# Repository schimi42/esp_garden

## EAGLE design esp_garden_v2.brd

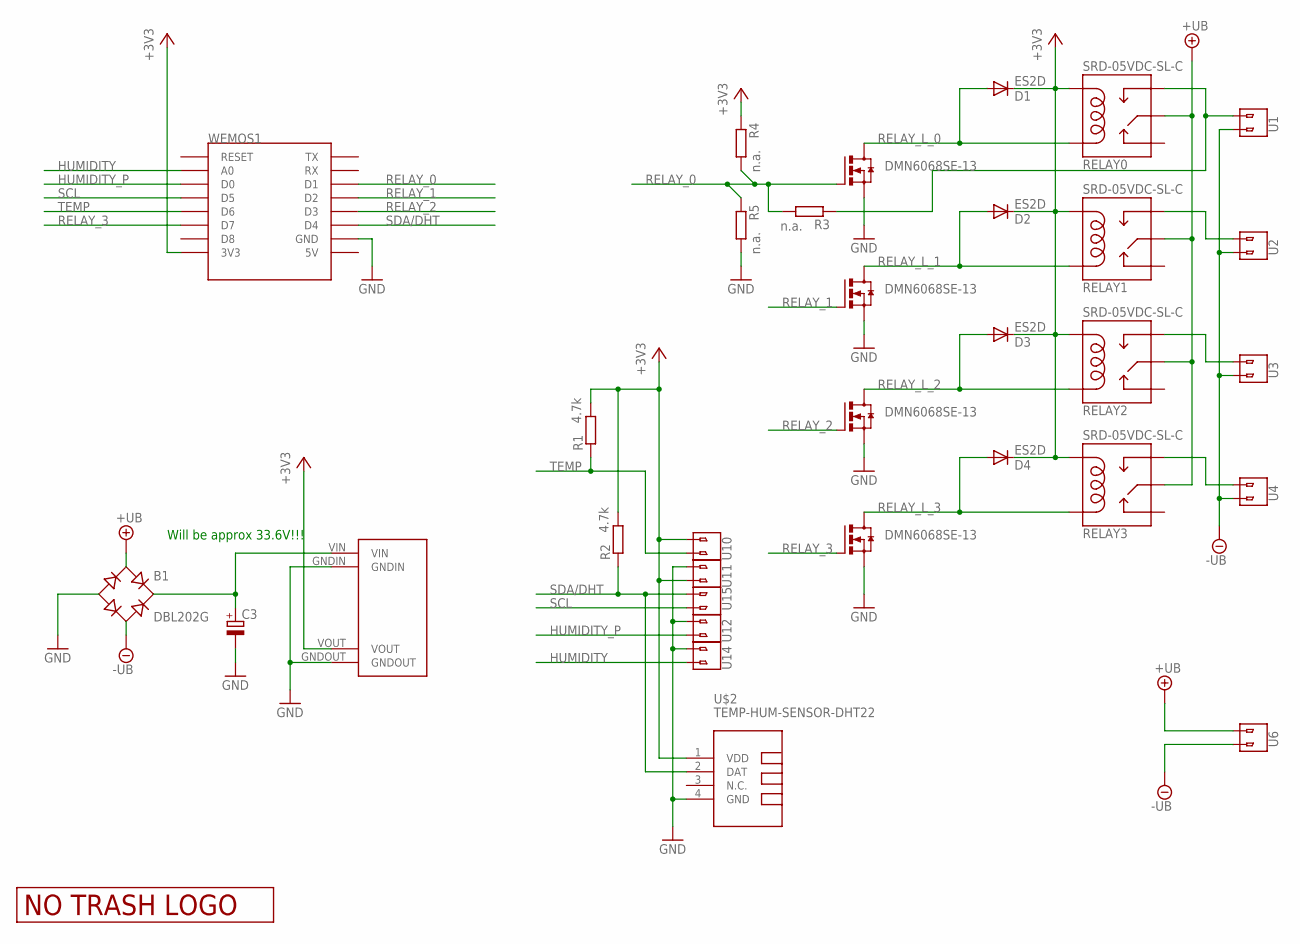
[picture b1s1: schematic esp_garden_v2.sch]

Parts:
B1: DBL202G; DB
C3: CPOL-EU150CLZ-0810; 150CLZ-0810
D1, D2, D3, D4: ES2D; SMB
R1, R2: 4.7k; M0805
R3, R4, R5: n.a.; M0805
RELAY0, RELAY1, RELAY2, RELAY3: SRD-05VDC-SL-C
T1, T2, T3, T4: DMN6068SE-13; SOT223
U1, U2, U3, U4, U6, U10, U11, U12, U14, U15: V1; 2_SCREW_PIN
U$1: LOGO_NO_TRASHNO_TRASH; LOGO_ROHS_NO_TRASH
U$2: TEMP-HUM-SENSOR-DHT22
U$3: MP1584EN
WEMOS1: WEMOS-D1-MINI

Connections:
+3V3: D1.C, D2.C, D3.C, D4.C, R1.2, R2.2, R4.1, RELAY0.COIL0, RELAY1.COIL0, RELAY2.COIL0, RELAY3.COIL0, U10.P$2 (2), U11.P$1 (1), U$2.1 (VDD), U$3.VOUT, WEMOS1.3V3
+UB: B1.AC1, RELAY0.SWCOMMON, RELAY1.SWCOMMON, RELAY2.SWCOMMON, RELAY3.SWCOMMON, U6.P$1 (1)
-UB: B1.AC2, U1.P$2 (2), U2.P$2 (2), U3.P$2 (2), U4.P$2 (2), U6.P$2 (2)
GND: B1.-, C3.-, R5.2, T1.3 (S), T2.3 (S), T3.3 (S), T4.3 (S), U11.P$2 (2), U12.P$2 (2), U14.P$2 (2), U$2.4 (GND), U$3.GNDIN, U$3.GNDOUT, WEMOS1.GND
HUMIDITY: U14.P$1 (1), WEMOS1.A0
HUMIDITY_P: U12.P$1 (1), WEMOS1.D0
unnamed: B1.+, C3.+, U$3.VIN
unnamed: R3.1, RELAY0.SWOPEN, U1.P$1 (1)
unnamed: RELAY1.SWOPEN, U2.P$1 (1)
unnamed: RELAY2.SWOPEN, U3.P$1 (1)
unnamed: RELAY3.SWOPEN, U4.P$1 (1)
RELAY_0: R3.2, R4.2, R5.1, T1.1 (G), WEMOS1.D1
RELAY_1: T2.1 (G), WEMOS1.D2
RELAY_2: T3.1 (G), WEMOS1.D3
RELAY_3: T4.1 (G), WEMOS1.D7
RELAY_L_0: D1.A, RELAY0.COIL1, T1.2 (D), T1.4 (D)
RELAY_L_1: D2.A, RELAY1.COIL1, T2.2 (D), T2.4 (D)
RELAY_L_2: D3.A, RELAY2.COIL1, T3.2 (D), T3.4 (D)
RELAY_L_3: D4.A, RELAY3.COIL1, T4.2 (D), T4.4 (D)
SCL: U15.P$2 (2), WEMOS1.D5
SDA/DHT: R2.1, U15.P$1 (1), U$2.2 (DAT), WEMOS1.D4
TEMP: R1.1, U10.P$1 (1), WEMOS1.D6

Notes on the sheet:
Will be approx 33.6V!!!

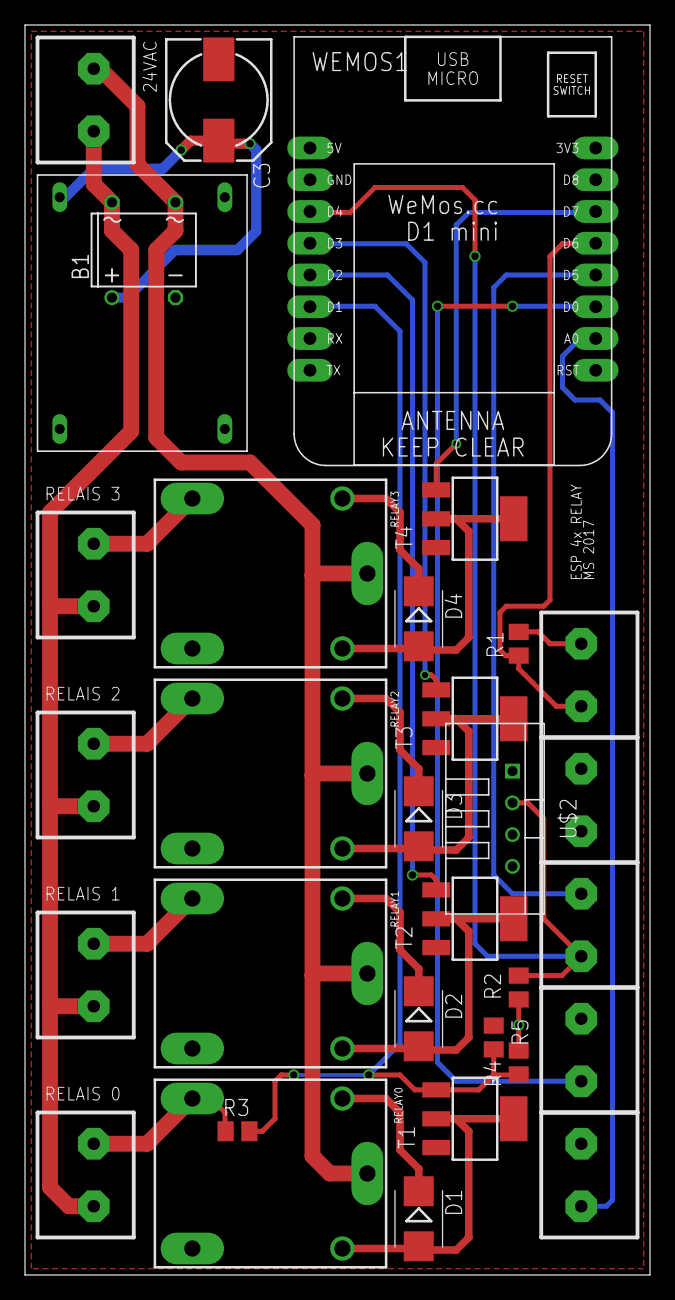
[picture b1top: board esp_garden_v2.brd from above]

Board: 2 copper layers, 50.0 x 100.0 mm, 33 parts (1 on the bottom side), 22 nets.

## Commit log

2017-03-03 Isolate for planes set to 0.254, added caps at LDO
2017-03-04 Added support for I2C sensor, changed LDO to REG1117
2017-03-06 Added text on PCB
2017-03-06 Optimized planes
2017-03-06 added options for DHT22 onboard and special use for relais 0
2017-03-06 added rectifier
2017-03-19 Initial commit for v2
2017-03-20 Ordered version

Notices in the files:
parts and their libraries:
diy-modules: Released under the Creative Commons Attribution 4.0 International License: http://creativecommons.org/licenses/by/4.0
JKW_CHIP: License : http://creativecommons.org/licenses/by-sa/3.0
(Creative Commons 3.0)
